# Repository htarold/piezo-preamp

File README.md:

Hi.

This is a simple high input impedance preamp.  I use it behind a
piezo transducer (MK1) that is repurposed as a hydrophone.  This
circuit can be made on a breadboard if desired.

Many preamp circuits are possible, but I needed one that had the
high input impedance for the piezo unit, and that would take a power
supply as low as 3.3V (it will happily take 5V too).  An alternative
would have been to use MCP6002, or other CMOS opamps, but the
circuit would not be any simpler.  So I went with a discrete JFET amp.

It's important that Q1 be a 2SK117-GR if you need to power the
preamp at 3.3V.  the -BL binned ones have a much higher bias point.
The 2SK117 is typically used in electret condenser mics; any JFET
used in electret condensers will work.

Q2 can be any small signal PNP.  The schematic shows an SMD version,
but the through-hole 2N3906 will be just fine.

R1 should be kept in the megohms, it determines the input impedance.
R5/R3 controls the gain, as shown the gain is about 130 which is
close to the max practical gain.  You can increase R3 to reduce the
gain, but you shouldn't change the R5 value too much. C1||C3 is
quite a large value, in order to retain low frequency response.  If
you aren't interested in low frequencies then you can use a lower
value like 4.uF electrolytic, and you won't need to parallel in a
ceramic cap.  As usual, you should decouple the supply input with
the largest cap (C2) you can afford that is appropriate to the kind
of supply you'll be using.

The preamp is not capacitively coupled!  So the output voltage
with no input (e.g. without the piezo unit connected) should be
around mid supply (1.65V with a 3.3V supply), but this will vary a
lot depending on the specific JFET characteristics.  It's not a
problem as long as it's at least a couple of hundred mV away from
the rails.  To move this Q-point you can change the value of R2 by
up to a factor of 2 up (to move the Q-point up) or down.

There is no output capacitor.  For some applications this is ok, but
add one if you're not certain.  Something like 0.1-10uF will be ok.

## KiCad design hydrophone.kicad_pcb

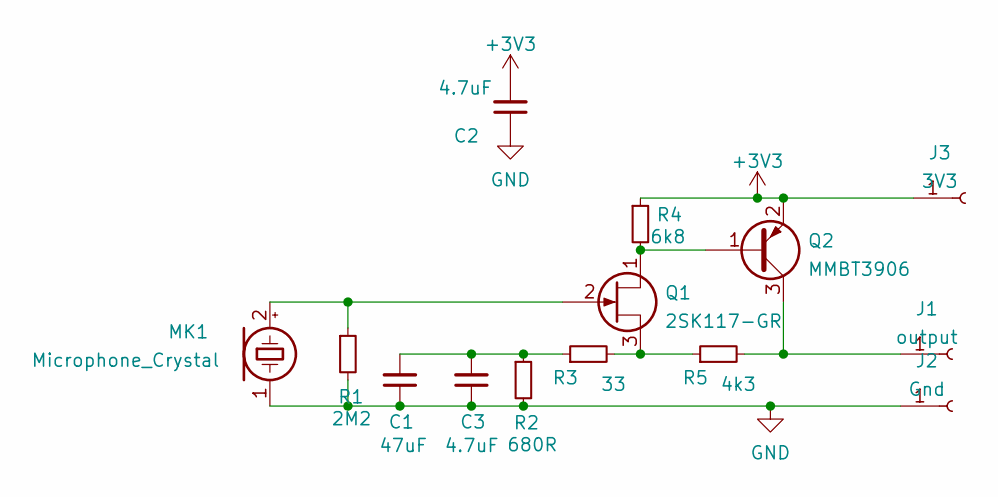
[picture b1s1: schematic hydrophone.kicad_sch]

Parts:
C1: 47uF; R_1206_3216Metric_Pad1.30x1.75mm_HandSolder
C2, C3: 4.7uF; R_0603_1608Metric
J1: output; PinHeader_1x01_P2.54mm_Vertical
J2: Gnd; PinHeader_1x01_P2.54mm_Vertical
J3: 3V3; PinHeader_1x01_P2.54mm_Vertical
MK1: Microphone_Crystal; US_transducer_40kHz_16mm
Q1: 2SK117-GR; TO-92_Inline_Horizontal1
Q2: MMBT3906; SOT-23
R1: 2M2; R_0603_1608Metric
R2: 680R; R_0603_1608Metric
R3: 33; R_0603_1608Metric
R4: 6k8; R_0603_1608Metric
R5: 4k3; R_0603_1608Metric

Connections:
+3V3: C2.2, J3.1, Q2.2 (E), R4.1
GND: C1.1, C2.1, C3.1, J2.1, MK1.1 (-), R1.2, R2.2
unnamed: C1.2, C3.2, R2.1, R3.1
unnamed: J1.1, Q2.3 (C), R5.2
unnamed: MK1.2 (+), Q1.2 (G), R1.1
unnamed: Q1.1 (D), Q2.1 (B), R4.2
unnamed: Q1.3 (S), R3.2, R5.1

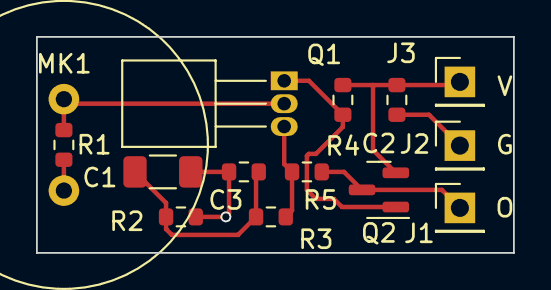
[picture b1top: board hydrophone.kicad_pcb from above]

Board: 2 copper layers, 26.5 x 12.0 mm, 14 parts (0 on the bottom side), 7 nets.

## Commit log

2022-05-13 Hi dusjagr!
2022-05-13 Create README.md
    Test commit
2022-05-13 deleted readme
2022-05-13 Added gerbers, etc.
